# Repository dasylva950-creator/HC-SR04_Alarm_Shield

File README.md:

# HC-SR04\_Alarm\_Shield

An Arduino UNO R3 proximity alarm shield with a custom KiCAD PCB layout

HC-SR04 Ultrasonic Alarm Shield

A custom Arduino Uno R3 shield that triggers an audible and visual alarm when an object enters a 50-centimeter threshold. This project combines embedded C++ programming, ultrasonic sensor integration, and a custom PCB designed in KiCad.

Features:

Precision Tracking: Uses the HC-SR04 ultrasonic sensor to calculate real-time distance.

Dual Alert System: Triggers a high-output active buzzer and a bright red LED simultaneously.

Custom Shield Form Factor: Designed to plug directly onto an Arduino Uno R3 without messy jumper wires.

Safety Threshold: Hardcoded 50cm boundary zone for immediate proximity alerts.

Hardware Components:

Microcontroller: Arduino Uno R3

Sensor: HC-SR04 Ultrasonic Distance Sensor

Indicators: 1x Active Buzzer, 1x Red LED

Passives: 1x 220Ω Resistor (for LED protection)

PCB: Custom designed dual-layer board

Pin Mapping:

VCC: Connect to the 5V pin on the Arduino.

Trig: Connect to digital Pin 9.

Echo: Connect to digital Pin 10.

GND: Connect to any GND pin on the Arduino.

Buzzer / LED (Positive): Connect to digital Pin 13 (through a 220Ω resistor for LEDs).

Buzzer / LED (Negative): Connect to GND

Software \& Engineering Challenges

The coding phase was the most challenging aspect of this project. Specifically, managing the precise timing required by the HC-SR04 sensor and handling signal bouncing issues required significant troubleshooting. 

How I Solved It:

1\. Pulse Timing: I utilized the `pulseIn()` function to accurately measure the microsecond travel time of the sound wave, converting it to centimeters using the speed of sound formula: `Distance = (Time \* 0.0343) / 2`.

2\. Logic Optimization: I implemented a strict conditional threshold check to prevent the buzzer and LED from lagging or stuttering when an object hovers exactly at the 50cm line.

Gallery \& Design Files

PCB Layout (KiCad)

\[KiCad PCB Layout](images/pcb\_layout.png)

Figure 1: 2D/3D render of the custom shield designed in KiCad.

You can prototype this project on a breadboard. 

Installation \& Usage

1\. Clone this repository:

&#x20;  ```bash

&#x20;  git clone https://github.com

&#x20;  ```

2\. Open `src/YOUR\_CODE\_FILE\_NAME.ino` in the Arduino IDE.

3\. Connect your Arduino Uno R3 via USB.

4\. Select Tools > Board > Arduino Uno\*\* and the correct COM port.

5\. Click Upload.

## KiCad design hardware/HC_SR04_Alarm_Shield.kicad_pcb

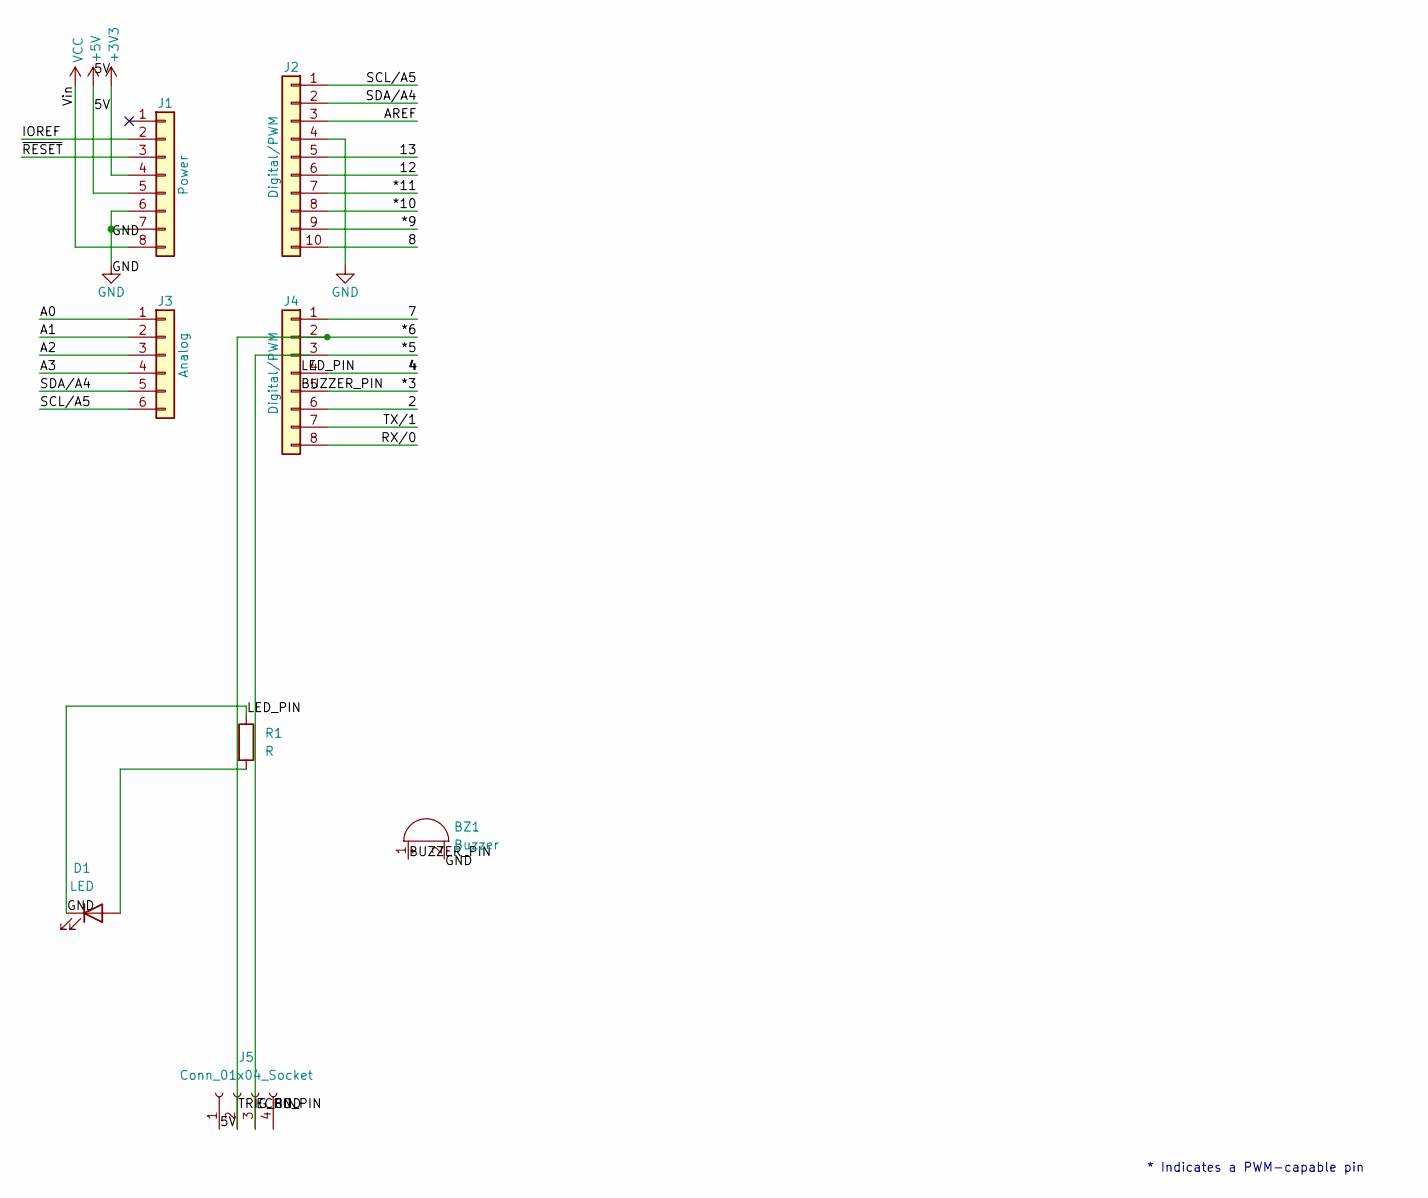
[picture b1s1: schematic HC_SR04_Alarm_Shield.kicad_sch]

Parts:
BZ1: Buzzer; Buzzer_12x9.5RM7.6
D1: LED; LED_D5.0mm
J1: Power; PinSocket_1x08_P2.54mm_Vertical
J2: Digital/PWM; PinSocket_1x10_P2.54mm_Vertical
J3: Analog; PinSocket_1x06_P2.54mm_Vertical
J4: Digital/PWM; PinSocket_1x08_P2.54mm_Vertical
J5: Conn_01x04_Socket; PinSocket_1x04_P2.54mm_Vertical
R1: R; R_Axial_DIN0207_L6.3mm_D2.5mm_P7.62mm_Horizontal

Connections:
+3V3: J1.4
+5V: J1.5, J5.1
/2: J4.6
/4: J4.4
/7: J4.1
/8: J2.10
/12: J2.6
/13: J2.5
/*3: J4.5
/*5: J4.3
/*9: J2.9
/*10: J2.8
/*11: J2.7
/A0: J3.1
/A1: J3.2
/A2: J3.3
/A3: J3.4
/AREF: J2.3
/BUZZER_PIN: BZ1.1 (+_1)
/ECHO_PIN: J5.3
/IOREF: J1.2
/RX/0: J4.8
/SCL/A5: J2.1, J3.6
/SDA/A4: J2.2, J3.5
/TX/1: J4.7
/~RESET: J1.3
unnamed: D1.2 (A), R1.2
VCC: J1.8

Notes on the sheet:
* Indicates a PWM-capable pin

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
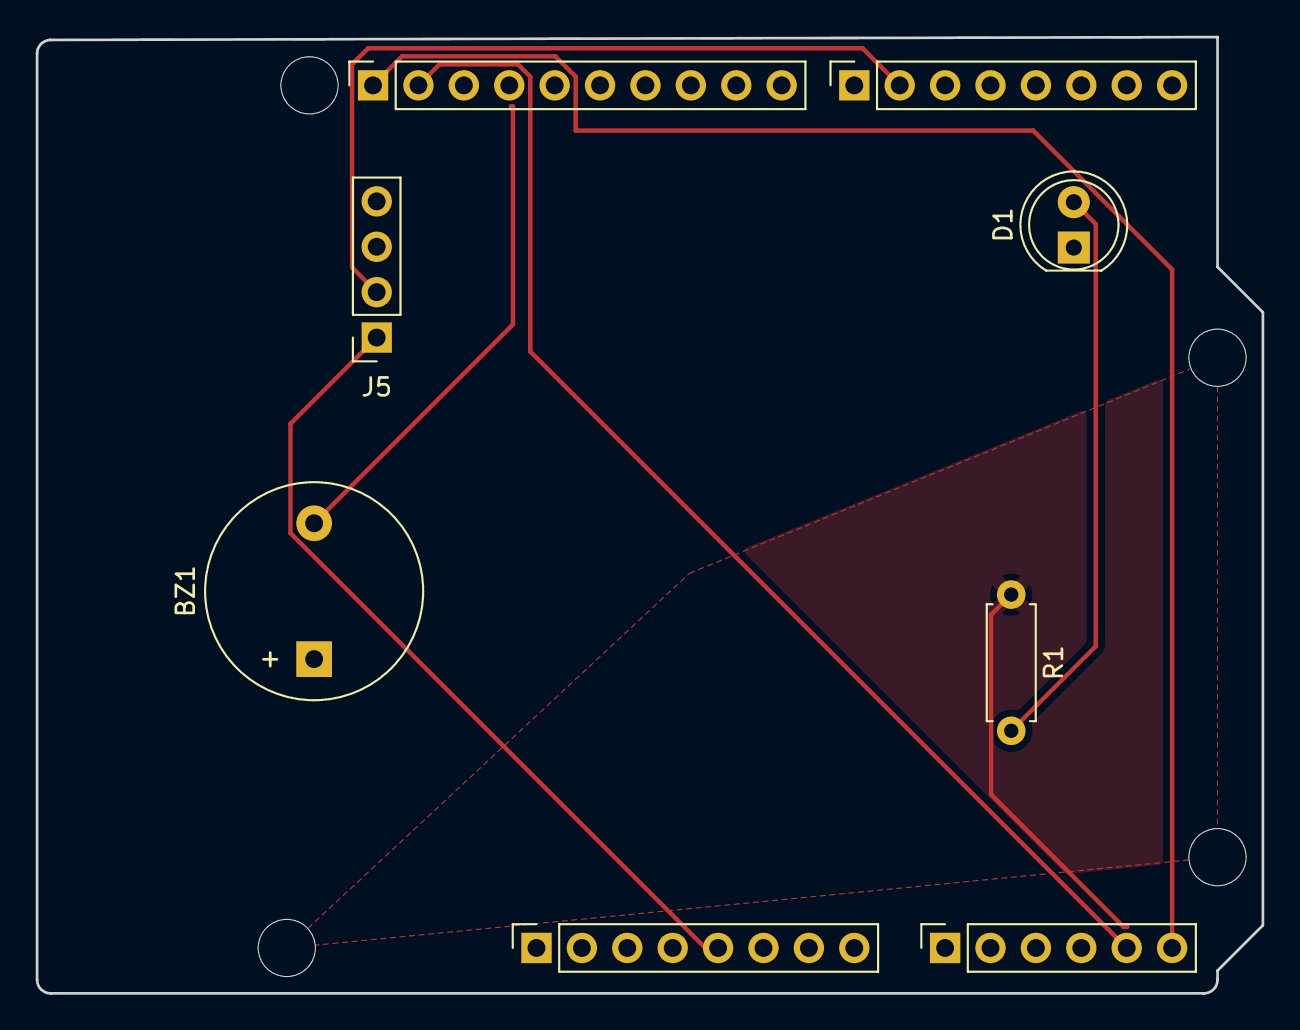
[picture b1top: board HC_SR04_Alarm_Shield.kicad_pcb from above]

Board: 2 copper layers, 68.6 x 53.5 mm, 12 parts (0 on the bottom side), 6 nets.

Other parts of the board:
MH1, MH2, MH3, MH4: MountingHole_3.2mm

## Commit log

2026-06-05 Initial commit: Add Arduino code, KiCad design files, and README
    Organized repository structure into src, hardware, and images folders. Updated documentation with components, pin mappings, and engineering challenges.
